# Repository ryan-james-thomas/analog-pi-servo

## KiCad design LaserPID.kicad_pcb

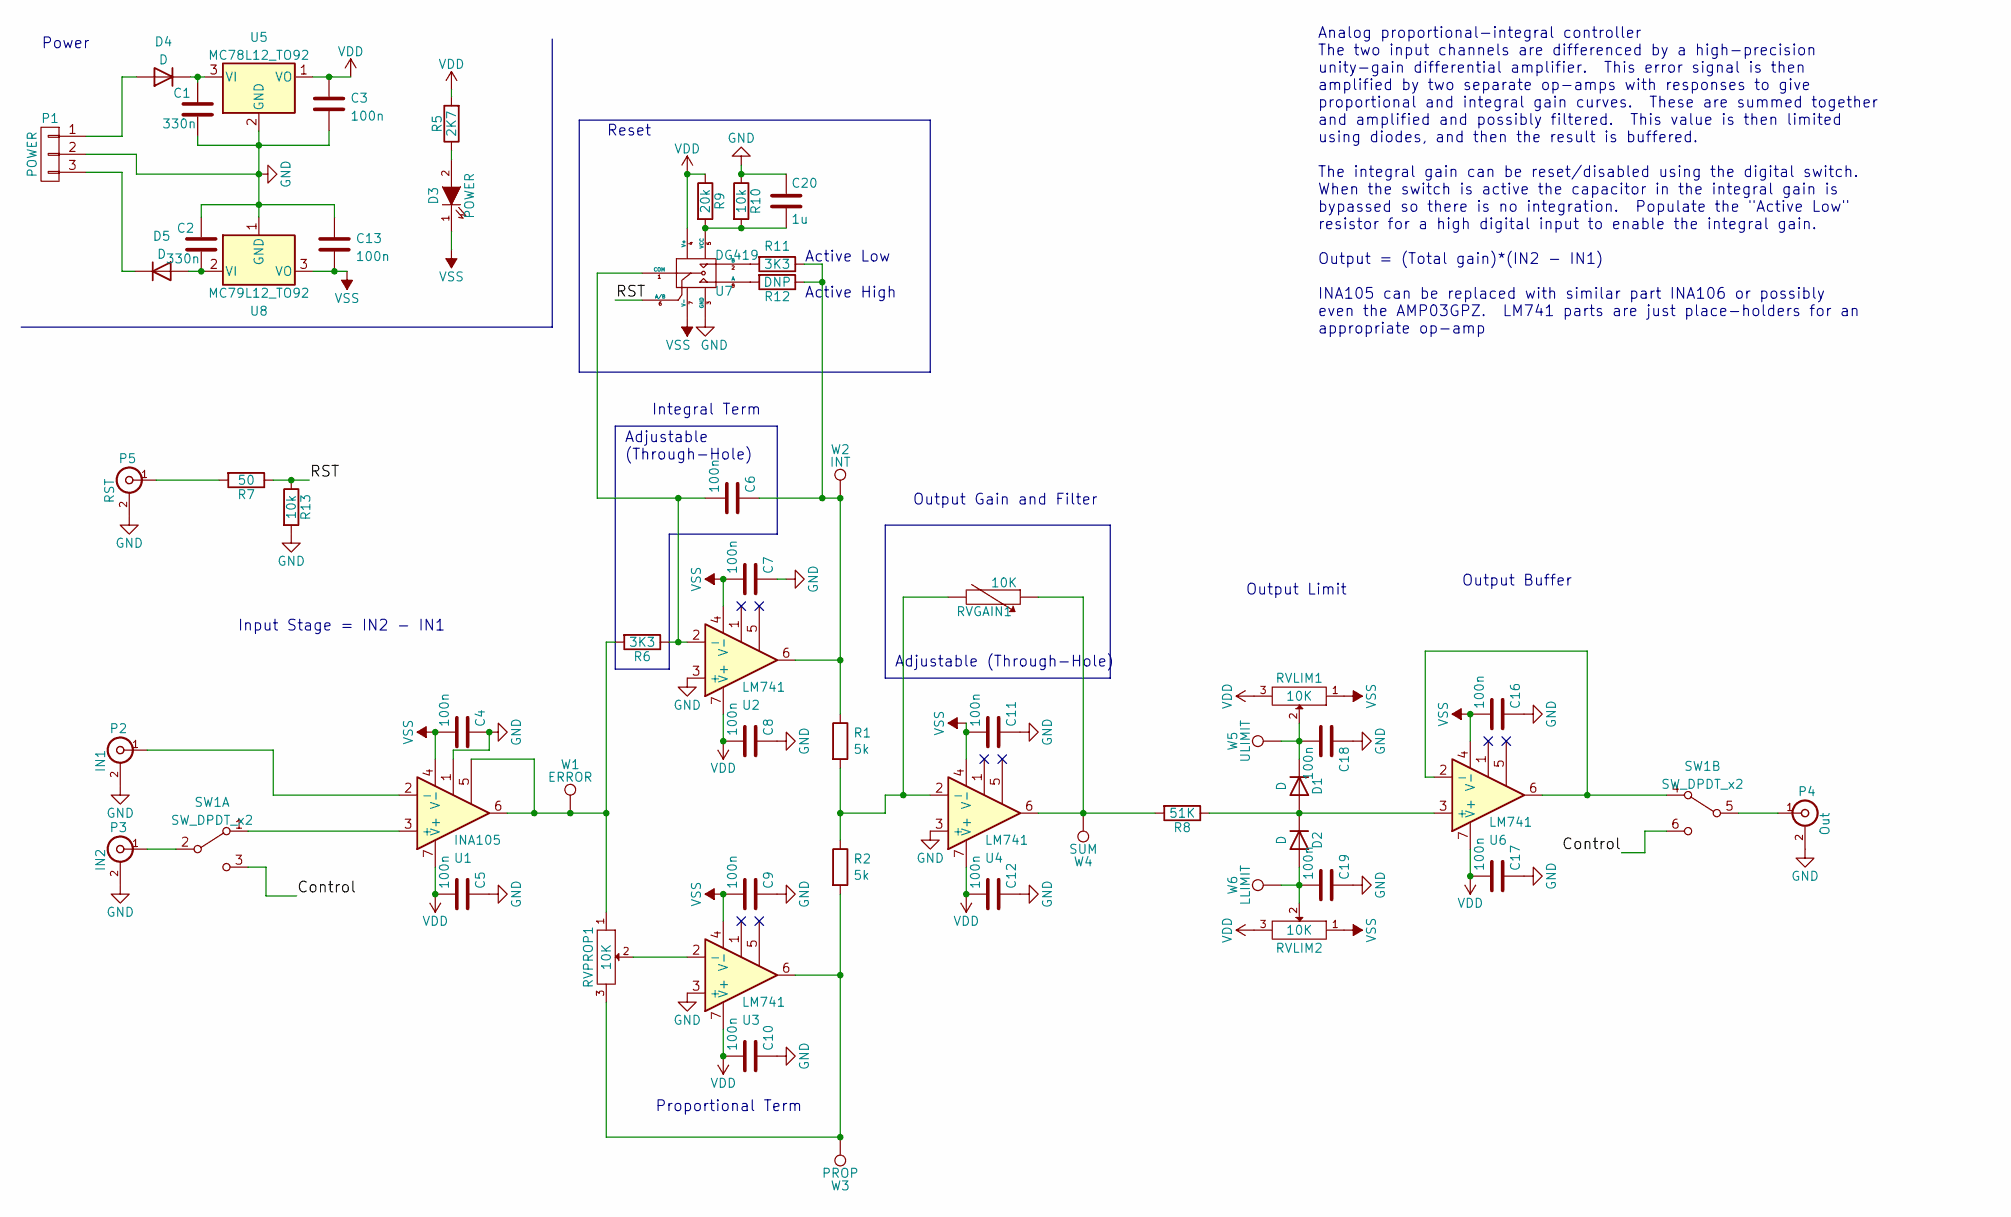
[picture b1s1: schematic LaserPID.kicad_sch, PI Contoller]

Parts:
C1, C2: 330n; C_1206_3216Metric_Pad1.33x1.80mm_HandSolder; Digikey Part Number 4713-GMC31X7R334K50NTCT-ND
C3, C4, C5, C7, C8, C9, C10, C11, C12, C13, C16, C17, C18, C19: 100n; C_1206_3216Metric_Pad1.33x1.80mm_HandSolder; Digikey Part Number 478-1556-1-ND
C6: 100n; R_Universal_L13.0mm_W4.0mm_P9.00mm
C20: 1u; C_1206_3216Metric_Pad1.33x1.80mm_HandSolder; Digikey Part Number 1276-2747-1-ND‎
D1, D2: D; D_DO-35_SOD27_P7.62mm_Horizontal; Digikey Part Number 1N4148FSCT-ND
D3: POWER; LED_D3.0mm; Digikey Part Number 732-5008-ND
D4, D5: D; D_1206_3216Metric_Pad1.42x1.75mm_HandSolder; Digikey Part Number 478-7806-1-ND
P1: POWER; TerminalBlock_bornier-3_P5.08mm; Digikey Part Number 2057-EBBA-03-C-SS-BU-ND
P2: IN1; BNC_Amphenol_B6252HB-NPP3G-50_Horizontal; Digikey Part Number ARF1690-ND
P3: IN2; BNC_Amphenol_B6252HB-NPP3G-50_Horizontal; Digikey Part Number ARF1690-ND
P4: Out; BNC_Amphenol_B6252HB-NPP3G-50_Horizontal; Digikey Part Number ARF1690-ND
P5: RST; BNC_Amphenol_B6252HB-NPP3G-50_Horizontal; Digikey Part Number ARF1690-ND
R1, R2: 5k; R_1206_3216Metric_Pad1.30x1.75mm_HandSolder; Digikey Part Number YAG5090CT-ND
R5: 2K7; R_1206_3216Metric_Pad1.30x1.75mm_HandSolder; Digikey Part Number RMCF1206JT2K70CT-ND
R6: 3K3; R_Universal_L13.0mm_W4.0mm_P9.00mm; Digikey Part Number RMCF1206JT3K30CT-ND
R7: 50; R_1206_3216Metric_Pad1.30x1.75mm_HandSolder; Digikey Part Number 541-2477-1-ND
R8: 51K; R_1206_3216Metric_Pad1.30x1.75mm_HandSolder; Digikey Part Number RMCF1206JT51K0CT-ND
R9: 20k; R_1206_3216Metric_Pad1.30x1.75mm_HandSolder; Digikey Part Number RMCF1206JT20K0CT-ND
R10, R13: 10k; R_1206_3216Metric_Pad1.30x1.75mm_HandSolder; Digikey Part Number RMCF1206JT10K0CT-ND
R11: 3K3; R_1206_3216Metric_Pad1.30x1.75mm_HandSolder; Digikey Part Number RMCF1206JT3K30CT-ND
R12: DNP; R_1206_3216Metric_Pad1.30x1.75mm_HandSolder
RVGAIN1: 10K; Potentiometer_Bourns_3296W_Vertical; Digikey Part Number 3296W-103LF-ND
RVLIM1, RVLIM2: 10K; Potentiometer_Bourns_3296W_Vertical; Digikey Part Number 3296W-103LF-ND
RVPROP1: 10K; Potentiometer_Bourns_3296W_Vertical; Digikey Part Number 3296W-103LF-ND
SW1: SW_DPDT_x2; DPDT_SW_ADAM_TECH; Digikey Part Number 2057-SW-T3-4B-A-A3-S2-ND
U1: INA105; DIP-8_W7.62mm_Socket; Digikey Part Number AMP03GPZ-ND
U2, U3, U4, U6: LM741; DIP-8_W7.62mm_Socket; Digikey Part Number 296-34251-5-ND
U5: MC78L12_TO92; TO-92_Inline; Digikey Part Number MC78L12ACPGOS-ND
U7: DG419; SOIC-8_3.9x4.9mm_P1.27mm; Digikey Part Number DG469EY-T1-E3CT-ND
U8: MC79L12_TO92; TO-92_Inline; Digikey Part Number MC79L12ACPGOS-ND
W1: ERROR; TestPoint_THTPad_D1.0mm_Drill0.5mm
W2: INT; TestPoint_THTPad_D1.0mm_Drill0.5mm
W3: PROP; TestPoint_THTPad_D1.0mm_Drill0.5mm
W4: SUM; TestPoint_THTPad_D1.0mm_Drill0.5mm
W5: ULIMIT; TestPoint_THTPad_D1.0mm_Drill0.5mm
W6: LLIMIT; TestPoint_THTPad_D1.0mm_Drill0.5mm

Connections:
/Control: SW1.3 (C), SW1.6 (C)
/RST: R7.1, R13.1, U7.6 (A/B)
GND: C1.2, C2.1, C3.2, C4.1, C5.1, C7.1, C8.1, C9.1, C10.1, C11.1, C12.1, C13.1, C16.1, C17.1, C18.1, C19.1, C20.1, P1.2, P2.2 (Ext), P3.2 (Ext), P4.2 (Ext), P5.2 (Ext), R10.1, R13.2, U1.1, U2.3 (+), U3.3 (+), U4.3 (+), U5.2 (GND), U7.3 (GND), U8.1 (GND)
unnamed: C6.1, R1.1, R11.1, R12.1, U2.6, W2.1
unnamed: C6.2, R6.1, U2.2 (-), U7.1 (COM)
unnamed 5: C18.2, D1.1 (K), RVLIM1.2, W5.1; also elsewhere on the board
unnamed 6: C19.2, D2.2 (A), RVLIM2.2, W6.1; also elsewhere on the board
unnamed: C20.2, R9.2, R10.2, U7.5 (VCC)
unnamed: D1.2 (A), D2.1 (K), R8.1, U6.3 (+)
unnamed: D3.2 (A), R5.1
unnamed: C1.1, D4.1 (K), U5.3 (VI)
unnamed: C2.2, D5.2 (A), U8.2 (VI)
unnamed: D4.2 (A), P1.1
unnamed: D5.1 (K), P1.3
unnamed: P2.1 (In), U1.2 (-)
unnamed: P3.1 (In), SW1.2 (B)
unnamed: P4.1 (In), SW1.5 (B)
unnamed: R1.2, R2.1, RVGAIN1.2, U4.2 (-)
unnamed: R2.2, RVPROP1.3, U3.6, W3.1
unnamed: R6.2, RVPROP1.1, U1.5, U1.6, W1.1
unnamed: P5.1 (In), R7.2
unnamed: R11.2, U7.2 (B)
unnamed: R12.2, U7.8 (A)
unnamed: R8.2, RVGAIN1.1, U4.6, W4.1
unnamed: RVPROP1.2, U3.2 (-)
unnamed: SW1.1 (A), U1.3 (+)
unnamed: SW1.4 (A), U6.2 (-), U6.6
VDD: C3.1, C5.2, C8.2, C10.2, C12.2, C17.2, R5.2, R9.1, RVLIM1.3, RVLIM2.3, U1.7 (V+), U2.7 (V+), U3.7 (V+), U4.7 (V+), U5.1 (VO), U6.7 (V+), U7.4 (V+); also elsewhere on the board
VSS: C4.2, C7.2, C9.2, C11.2, C13.2, C16.2, D3.1 (K), RVLIM1.1, RVLIM2.1, U1.4 (V-), U2.4 (V-), U3.4 (V-), U4.4 (V-), U6.4 (V-), U7.7 (V-), U8.3 (VO); also elsewhere on the board

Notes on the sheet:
Reset
Output Limit
Active High
Proportional Term
Input Stage = IN2 - IN1
Analog proportional-integral controller The two input channels are differenced by a high-precision unity-gain differential amplifier. This error signal is then amplified by two separate op-amps with responses to give proportional and integral gain curves. These are summed together and amplified and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
Output Buffer
Output Gain and Filter
Power
Adjustable (Through-Hole)
Integral Term
Active Low
Adjustable (Through-Hole)

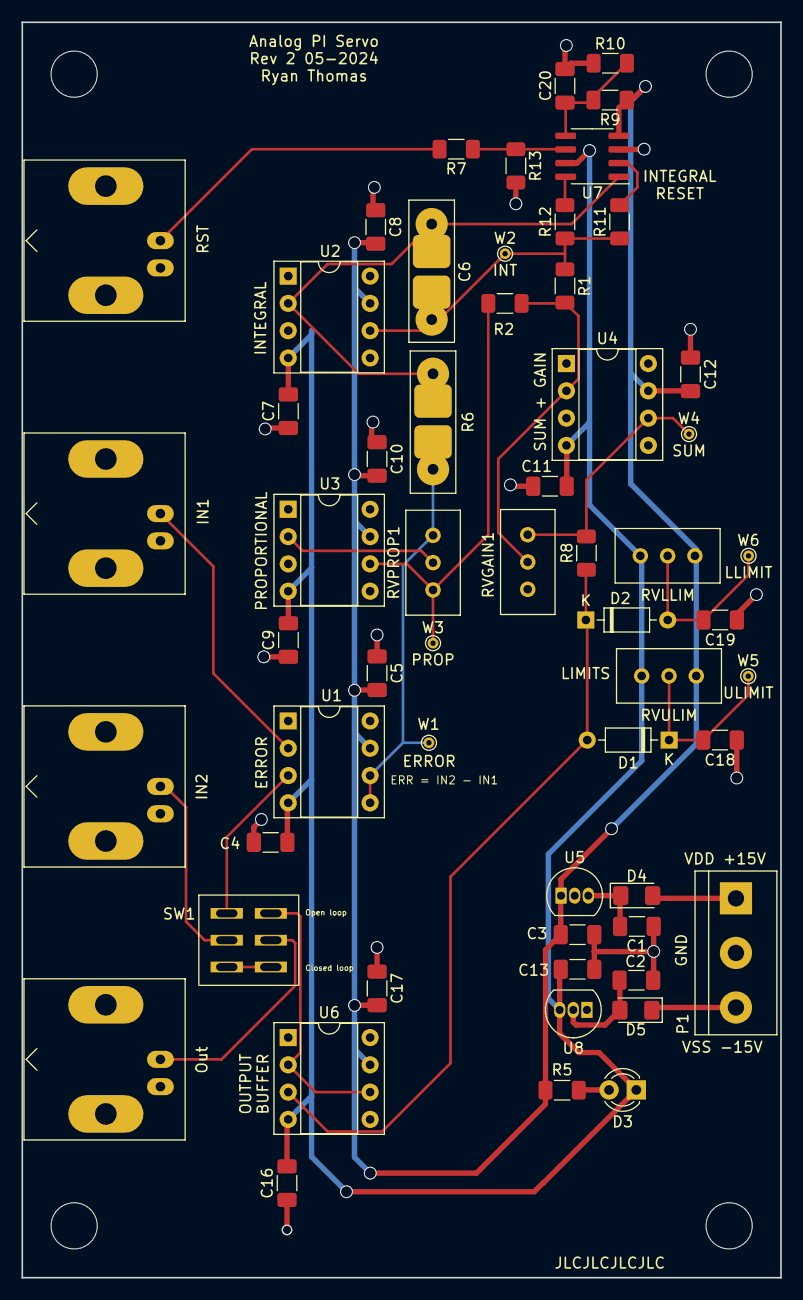
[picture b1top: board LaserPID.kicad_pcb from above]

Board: 2 copper layers, 70.6 x 116.8 mm, 58 parts (0 on the bottom side), 29 nets.

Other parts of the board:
RVLLIM: 10K; Potentiometer_Bourns_3296W_Vertical
RVULIM: 10K; Potentiometer_Bourns_3296W_Vertical

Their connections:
unnamed 5: RVULIM.2; also elsewhere on the board
unnamed 6: RVLLIM.2; also elsewhere on the board
VDD: RVLLIM.3, RVULIM.3; also elsewhere on the board
VSS: RVLLIM.1, RVULIM.1; also elsewhere on the board

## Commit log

2024-05-06 Some updates to part list for no-longer-available parts
2024-05-07 Update to board with over- and reverse-voltage protection.
    Smaller board as well to fit in boxes from Digikey. All BNCs on
    the same side, power on opposite side. Switch included to go between
    open and closed loop control
2024-05-08 Updated board, sent for production
